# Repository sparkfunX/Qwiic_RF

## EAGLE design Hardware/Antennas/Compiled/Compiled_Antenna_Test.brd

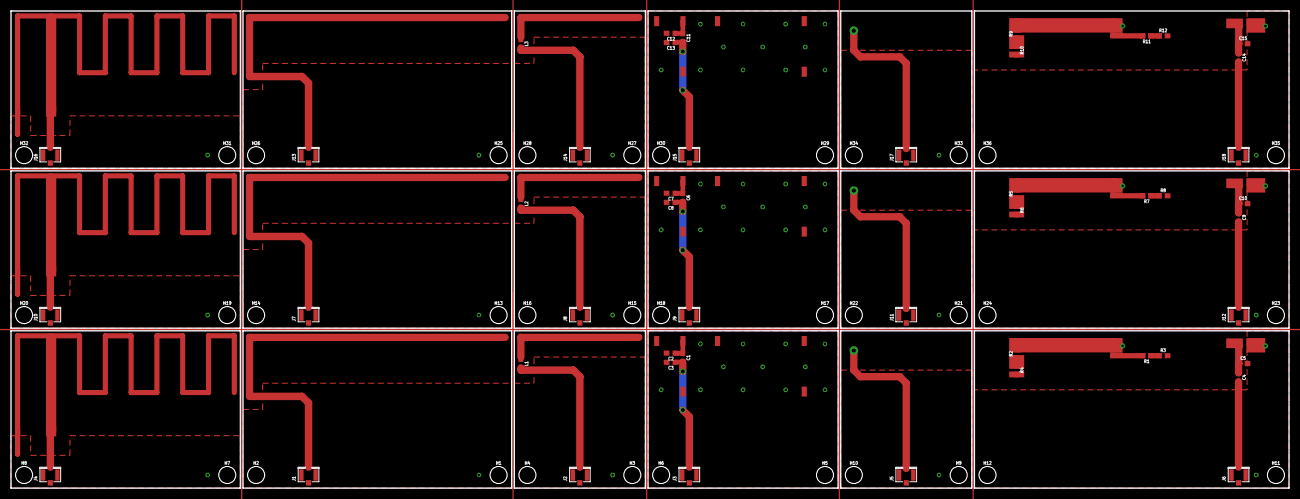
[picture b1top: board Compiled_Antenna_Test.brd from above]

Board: 2 copper layers, 247.7 x 92.5 mm, 93 parts (0 on the bottom side), 45 nets.

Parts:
C1, C4, C6, C9, C11, C14: 4.7pF; 0603
C2, C3, C5, C7, C8, C10, C12, C13, C15: 1.0pF; 0603
H1, H2, H3, H4, H5, H6, H7, H8, H9, H10, H11, H12, H13, H14, H15, H16, H17, H18, H19, H20, H21, H22, H23, H24, H25, H26, H27, H28, H29, H30, H31, H32, H33, H34, H35, H36: STAND-OFF
J1, J2, J3, J4, J5, J6, J7, J8, J9, J10, J11, J12, J13, J14, J15, J16, J17, J18: U.FL
L1, L2, L3: 33nH/±5%/500mA; 0603
R1, R2, R3, R4, R5, R6, R7, R8, R9, R10, R11, R12: 0; 0603
U$1, U$4, U$7: ONBOARD_SMD_STAMPED
U$2, U$5, U$8: ANTENNA_915MHZ_INVERTED_F; ANTENNA_INVERTED_F_915MHZ
U$3, U$6, U$9: ETHERTRONICS_STAMPED_ANTENNA; ETHERTRONICS_ISM_STAMPED

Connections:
FEED1: J2.FEED, L1.2
FEED2: C1.1, C2.1, U$1.FEED
FEED3: J4.FEED, U$2.FEED
FEED5: C4.1, C5.1, U$3.FEED
FEED7: J8.FEED, L2.2
FEED8: C6.1, C7.1, U$4.FEED
FEED9: J10.FEED, U$5.FEED
FEED11: C9.1, C10.1, U$6.FEED
FEED13: J14.FEED, L3.2
FEED14: C11.1, C12.1, U$7.FEED
FEED15: J16.FEED, U$8.FEED
FEED17: C14.1, C15.1, U$9.FEED
GND: J1.1, J1.2
GND1: J2.1, J2.2
GND2: C2.2, C3.2, J3.1, J3.2, U$1.GND
GND3: J4.1, J4.2, U$2.GND
GND4: J5.1, J5.2
GND5: C5.2, J6.1, J6.2, U$3.GND
GND6: J7.1, J7.2
GND7: J8.1, J8.2
GND8: C7.2, C8.2, J9.1, J9.2, U$4.GND
GND9: J10.1, J10.2, U$5.GND
GND10: J11.1, J11.2
GND11: C10.2, J12.1, J12.2, U$6.GND
GND12: J13.1, J13.2
GND13: J14.1, J14.2
GND14: C12.2, C13.2, J15.1, J15.2, U$7.GND
GND15: J16.1, J16.2, U$8.GND
GND16: J17.1, J17.2
GND17: C15.2, J18.1, J18.2, U$9.GND
unnamed: C1.2, C3.1, J3.FEED
unnamed: C4.2, J6.FEED
unnamed: R2.1, R4.1
unnamed: R1.1, R3.1
unnamed: C6.2, C8.1, J9.FEED
unnamed: C9.2, J12.FEED
unnamed: R5.1, R6.1
unnamed: R7.1, R8.1
unnamed: C11.2, C13.1, J15.FEED
unnamed: C14.2, J18.FEED
unnamed: R9.1, R10.1
unnamed: R11.1, R12.1
STRIP1: R1.2, R4.2
STRIP3: R6.2, R7.2
STRIP5: R10.2, R11.2

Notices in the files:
parts and their libraries:
SparkFun-Connectors: Licensing: Creative Commons ShareAlike 4.0 International - https://creativecommons.org/licenses/by-sa/4.0
